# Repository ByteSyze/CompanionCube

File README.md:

3D-LED-Companion-Cube
=====================

This 3D LED Companion Cube project will contain all necessary information to create a 3D printed companion cube with an
internal circuit to make the hearts flash.
_____________________

The original companion cube model was created by Poh and downloaded from thingiverse here: http://www.thingiverse.com/thing:33138
_____________________
The circuit is based on an attiny13 MCU, that will require additional hardware to program 
(e.g. AVR mkII or ATMEL-ICE). All schematics and circuits are designed in KiCAD.

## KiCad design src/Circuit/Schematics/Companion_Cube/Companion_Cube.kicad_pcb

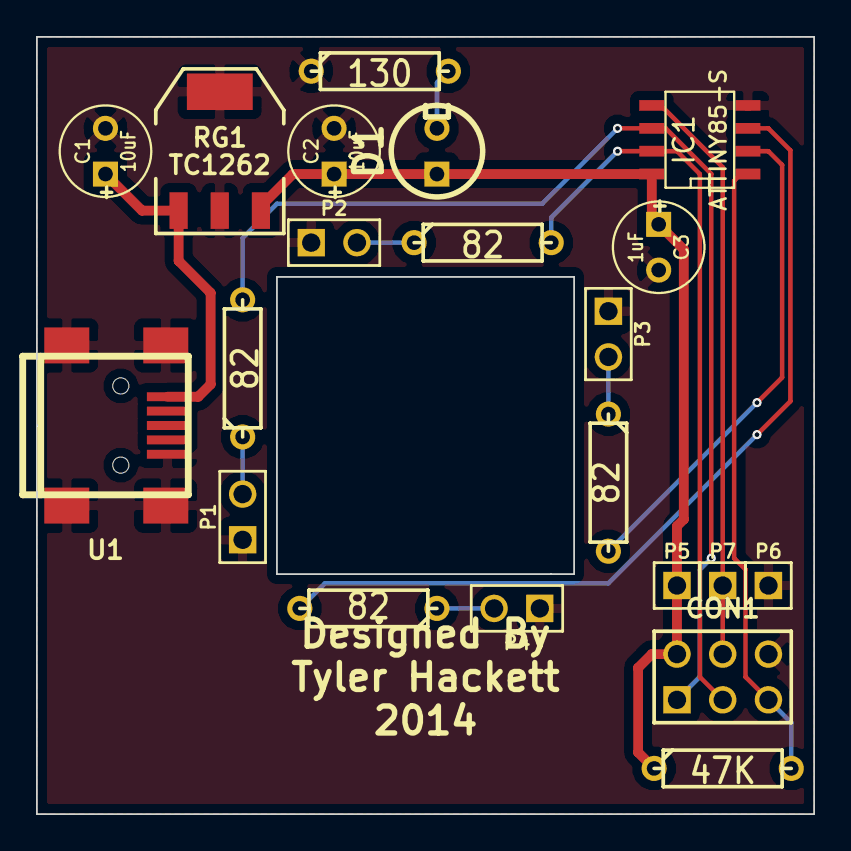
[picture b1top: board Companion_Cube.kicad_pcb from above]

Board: 2 copper layers, 43.2 x 43.2 mm, 21 parts (0 on the bottom side), 14 nets.

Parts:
C1, C2: 10uF; C1V5
C3: 1uF; C1V5
CON1: AVR-ISP-6; pin_array_3x2
D1: RED; LEDV
IC1: ATTINY85-S; SO8E
P1: LED_4; PIN_ARRAY_2X1
P2: LED_3; PIN_ARRAY_2X1
P3: LED_2; PIN_ARRAY_2X1
P4: LED_1; PIN_ARRAY_2X1
P5, P6, P7: CONN_1; PIN_ARRAY_1
R1, R2, R3, R4: 82; R3
R5: 130; R3
R6: 47K; R3
RG1: TC1262; SOT223
U1: MINI-B_USB; USB_MINI_B

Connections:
GND: C1.2, C2.2, C3.2, CON1.6, IC1.4, P1.1, P2.1, P3.1, P4.1, P6.1, R5.1, RG1.2, RG1.4, U1.5, U1.6, U1.7, U1.8, U1.9
unnamed: CON1.5, IC1.1, R6.2
unnamed: CON1.4, IC1.5, P7.1
unnamed: IC1.3, R4.2
unnamed: IC1.2, R3.2
unnamed: CON1.3, IC1.7, R2.2
unnamed: CON1.1, IC1.6, R1.2
unnamed: P4.2, R4.1
unnamed: D1.2, R5.2
unnamed: P3.2, R3.1
unnamed: P2.2, R2.1
unnamed: P1.2, R1.1
unnamed: C1.1, RG1.1, U1.1
VCC: C2.1, C3.1, CON1.2, D1.1, IC1.8, P5.1, R6.1, RG1.3

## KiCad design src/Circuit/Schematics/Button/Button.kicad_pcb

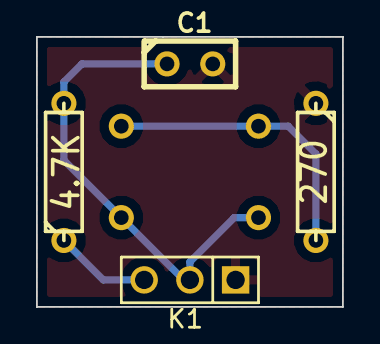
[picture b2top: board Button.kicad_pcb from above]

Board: 2 copper layers, 17.0 x 15.0 mm, 5 parts (1 on the bottom side), 4 nets.

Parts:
C1: 10nF; C1
K1: CONN_3; PIN_ARRAY_3X1
R1: 4.7K; R3
R2: 270; R3
SW1: SW_PUSH; SW_PUSH_SMALL

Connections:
GND: C1.2, K1.1, R2.1
unnamed: R2.2, SW1.2
unnamed: C1.1, K1.2, R1.2, SW1.1
VCC: K1.3, R1.1

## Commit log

2014-12-04 :space_invader: Added .gitattributes & .gitignore files
2014-12-04 Added initial files
2014-12-04 Added regulator, AVR ISP header
2014-12-05 Better origins on models
2014-12-05 Fixed backwards facing normal on cube lid
2014-12-05 Fixes to overlap in top of model
    With any luck, the top lid will now fit seamlessly.
2014-12-05 Thicker walls on container
2014-12-05 Fixes to wall thickness
    Last changes accidentally resized a little too much. This should fix
    changes to the walls of the container and lid.
2014-12-05 Removed use of reset pin from LED controller
    The walls of the lid have also been shortened for slightly quicker
    printing.
2014-12-05 Added button schematic
    The button will be on a separate PCB so that it can be placed at the
    other side of the cube.
    The button includes a capacitor for debounce and an extra resistor as a
    precaution, incase the button is ever connected to an output*.
    *Should be safe for up to 5v, passing 20ma which is pretty common for
    MCU I/O. Requires atleast a 1/10W dissipation.
2014-12-05 Fixed inclusion of container in lid STL
    This is way too easy to do.
2014-12-05 Changes to cube model.
2014-12-05 Added version of cube with micro usb cutout
2014-12-06 Moved debounce capacitor to behind the switch
2014-12-06 Created button circuit
2014-12-06 Initial LED driver circuit
2014-12-06 Connected remaining ratsnets, added some logoz
2014-12-07 Middle of lid is now flush with the outer rim
    The structures added by the printer make things a bigger pain than they
    should be.
2014-12-07 Added support in center of container
    The button for initiating blinky lights will sit on top of this support
    and be glued on top due to me being too lazy to think of a better way to
    attach it.
2014-12-07 Fixed incorrect references to the Mini USB slot
    Everything until now that has referred to USB Micro is actually USB
    Mini. Been working too much with micro's it seems.
2014-12-11 Redesigning circuit board for new model
2014-12-11 Connected ratsnet, added some personalization
2014-12-11 Attached mini USB shield pads to GND
2014-12-11 Reorganizing
2014-12-11 Added attiny85 DIP version
2014-12-11 Generated gerber files for button PCB
2014-12-11 Initial code
    Project is set up in Atmel Studio.
2014-12-11 Testing out functions
    Code works thus far.
2014-12-11 Added timer initialization
2014-12-11 Include cpufunc.h header file, change toggle_pin()
2014-12-11 Added LED macros and display_number() function
2014-12-11 Fixed always on PB1 in display_number()
2014-12-11 Fixed LED timing.
    The LEDs will flash a sequence of 3,4,1,2, then pause briefly and
    repeat.
2014-12-12 Added a simple startup light sequence.
2014-12-12 Fixed timing issue in start up
2014-12-17 Widened hole on cube circuit, smaller button PCB
2014-12-17 Adjusted the pin header on button PCB
2014-12-18 Cleaned up wiring to attiny on PCB
2014-12-27 Removed center pillar on container model
    The button will no longer rest on the pillar. Instead, the lid will be 2
    separate models with the button in the middle.
2015-01-08 Modifications to model
    Flattened the bottom of the box lid, removed center pillar in container,
    improved placement and thickness of USB mini port, added a button holder
    mesh.
2015-01-16 Remove outdated circuit
    The SMD version of the board is not worth the extra effort, and the DIP
    versions are now known to work correctly.
2016-10-14 Remove excess files.
